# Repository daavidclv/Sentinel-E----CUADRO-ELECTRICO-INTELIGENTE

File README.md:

# ⚡ Sentinel-E — Cuadro Eléctrico Inteligente

Proyecto de asignatura: diseño de un cuadro eléctrico con funcionalidades automatizadas de protección, monitorización y control remoto vía servidor HTTP.

> **Estado: FINALIZADO** — este repositorio contiene actualmente el proyecto completo. El firmware (C/C++ sobre STM32) esta ya todo subido, los diseños del circuito y la memoria con sus respectivos manuales.

## 📋 Descripción

Sentinel-E es un cuadro eléctrico inteligente pensado para integrar en un mismo sistema:
- **Protección** eléctrica automatizada
- **Monitorización** en tiempo real de las variables del cuadro
- **Control remoto** mediante un servidor HTTP embebido

## 🛠️ Stack técnico previsto

- **Microcontrolador:** STM32 (C/C++, HAL)
- **Comunicación:** servidor HTTP embebido para control/monitorización remota

## 📄 Documentación

`Memoria_Tecnica_SENTINEL-E.pdf` - Memoria Tecnica del proyecto incluye manual y fotos del mismo.

`Propuesta_SentinelE_REVISADA_v3.pdf` — propuesta técnica del proyecto con el planteamiento, objetivos y arquitectura prevista

## 👤 Autor

David Calvo Heredero — [LinkedIn](https://www.linkedin.com/in/david-calvo-heredero-20b20a33a) · [GitHub](https://github.com/daavidclv)

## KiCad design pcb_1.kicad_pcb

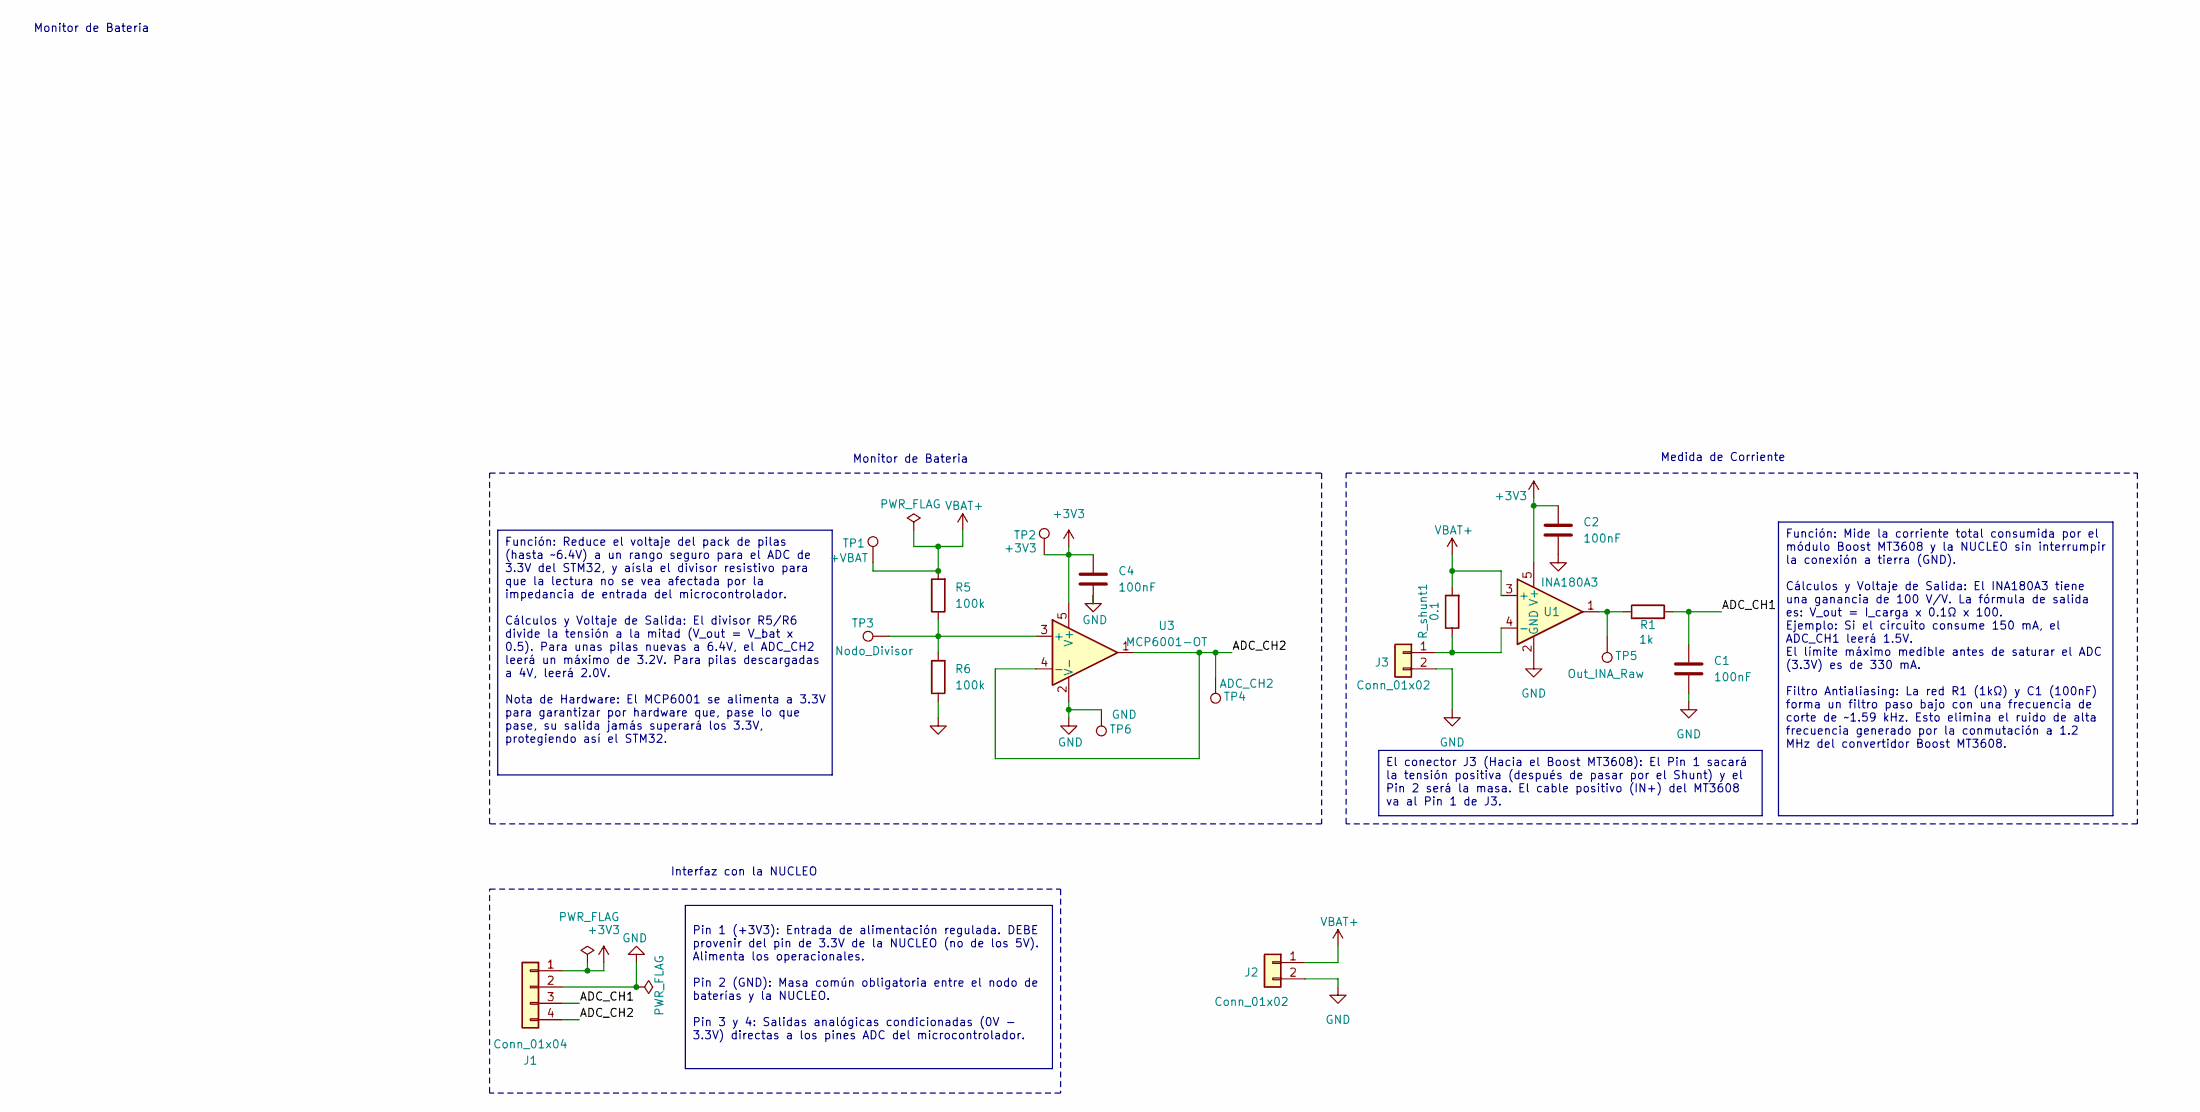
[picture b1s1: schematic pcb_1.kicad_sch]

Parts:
C1, C2, C4: 100nF; C_Disc_D3.0mm_W1.6mm_P2.50mm
J1: Conn_01x04; TerminalBlock_Phoenix_MKDS-1,5-4-5.08_1x04_P5.08mm_Horizont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
J2, J3: Conn_01x02; TerminalBlock_Phoenix_MKDS-1,5-2-5.08_1x02_P5.08mm_Horizont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
R1: 1k; R_Axial_DIN0207_L6.3mm_D2.5mm_P10.16mm_Horizontal
R5, R6: 100k; R_Axial_DIN0207_L6.3mm_D2.5mm_P10.16mm_Horizontal
R_shunt1: 0.1; R_Axial_DIN0411_L9.9mm_D3.6mm_P12.70mm_Horizontal
TP1: +VBAT; Pin_D0.9mm_L10.0mm_W2.4mm_FlatFork
TP2: +3V3; Pin_D0.9mm_L10.0mm_W2.4mm_FlatFork
TP3: Nodo_Divisor; Pin_D0.9mm_L10.0mm_W2.4mm_FlatFork
TP4: ADC_CH2; Pin_D0.9mm_L10.0mm_W2.4mm_FlatFork
TP5: Out_INA_Raw; Pin_D0.9mm_L10.0mm_W2.4mm_FlatFork
TP6: GND; Pin_D0.9mm_L10.0mm_W2.4mm_FlatFork
U1: INA180A3; SOT-23-5
U3: MCP6001-OT; SOT-23-5

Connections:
+3V3: C2.1, C4.1, J1.1, TP2.1, U1.5 (V+), U3.5 (V+)
/ADC_CH1: C1.1, J1.3, R1.2
/ADC_CH2: J1.4, TP4.1, U3.1, U3.4 (-)
GND: C1.2, C2.2, C4.2, J1.2, J2.2, J3.2, R6.1, TP6.1, U1.2 (GND), U3.2 (V-)
unnamed: J3.1, R_shunt1.1, U1.4 (-)
unnamed: R1.1, TP5.1, U1.1
unnamed: R5.1, R6.2, TP3.1, U3.3 (+)
VBAT+: J2.1, R5.2, R_shunt1.2, TP1.1, U1.3 (+)

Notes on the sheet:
Función: Reduce el voltaje del pack de pilas (hasta ~6.4V) a un rango seguro para el ADC de 3.3V del STM32, y aísla el divisor resistivo para que la lectura no se vea afectada por la impedancia de entrada del microcontrolador. Cálculos y Voltaje de Salida: El divisor R5/R6 divide la tensión a la mi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
El conector J3 (Hacia el Boost MT3608): El Pin 1 sacará la tensión positiva (después de pasar por el Shunt) y el Pin 2 será la masa. El cable positivo (IN+) del MT3608 va al Pin 1 de J3.
Función: Mide la corriente total consumida por el módulo Boost MT3608 y la NUCLEO sin interrumpir la conexión a tierra (GND). Cálculos y Voltaje de Salida: El INA180A3 tiene una ganancia de 100 V/V. La fórmula de salida es: V_out = I_carga x 0.1Ω x 100. Ejemplo: Si el circuito consume 150 mA, el AD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
Pin 1 (+3V3): Entrada de alimentación regulada. DEBE provenir del pin de 3.3V de la NUCLEO (no de los 5V). Alimenta los operacionales. Pin 2 (GND): Masa común obligatoria entre el nodo de baterías y la NUCLEO. Pin 3 y 4: Salidas analógicas condicionadas (0V - 3.3V) directas a los pines ADC del micr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
Medida de Corriente
Monitor de Bateria
Interfaz con la NUCLEO

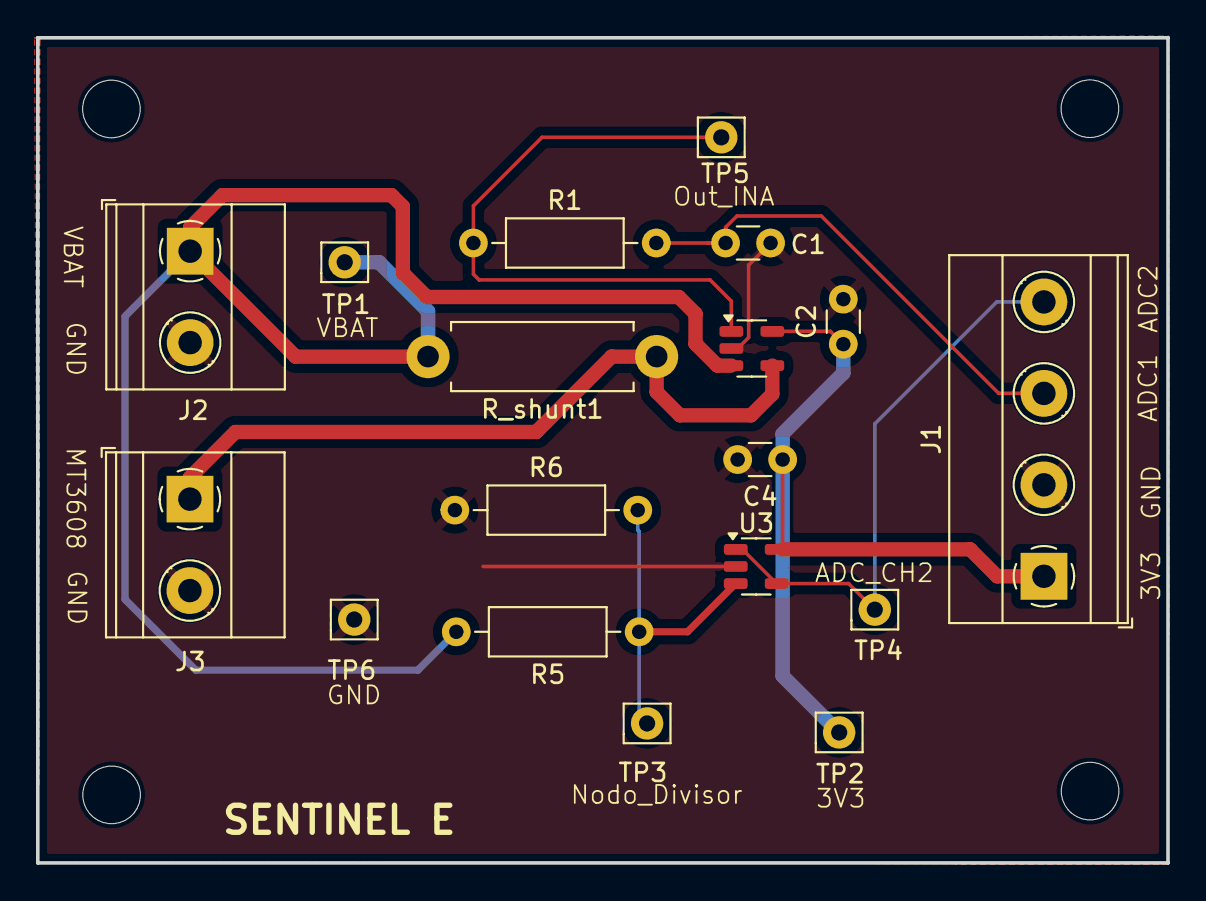
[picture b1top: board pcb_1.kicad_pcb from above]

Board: 2 copper layers, 62.8 x 45.8 mm, 18 parts (0 on the bottom side), 8 nets.

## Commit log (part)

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2026-05-15 NUCLEO A a medio hacer 80%
2026-05-15 NUCLEO-B a medio hacer 75%
2026-05-15 PCB terminada
